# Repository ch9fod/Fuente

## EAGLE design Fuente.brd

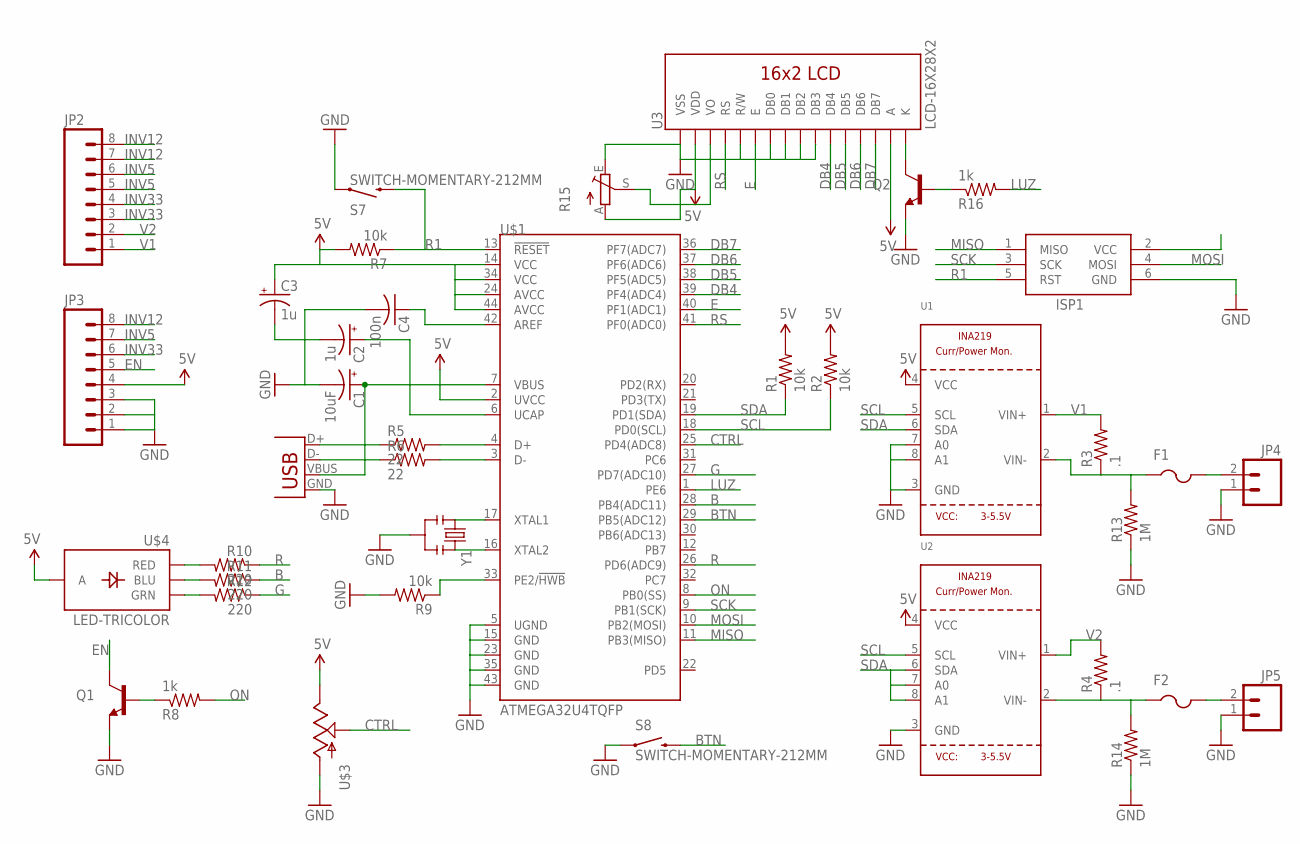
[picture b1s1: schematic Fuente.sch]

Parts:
C1: 10uF; CPOL-RADIAL-10UF-25V
C2, C3: 1u; E2,5-6
C4: 100n; C0805K
F1, F2: PTCFUSE-1812; 1812
ISP1: AVRISP-6; AVRISP
JP1: USBSMD; USB-MINIB
JP2, JP3: M08LONGPADS; 1X08_LONGPADS
JP4, JP5: M02LOCK_LONGPADS; 1X02_LOCK_LONGPADS
Q1, Q2: TRANSISTOR_NPNSOT23; SOT23
R1, R2, R7, R9: 10k; M0805
R3, R4: .1; R2512
R5, R6: 22; 0309/12
R8, R16: 1k; M0805
R10, R11, R12: 220; 0805
R13, R14: 1M; M0805
R15: TRIM_EU-CT6; CT6
S7, S8: SWITCH-MOMENTARY-212MM; TACTILE-PTH-12MM
U1, U2: INA219; SOT23-8
U3: LCD-16X28X2; LCD-8X2
U$1: ATMEGA32U4TQFP; SPARKFUN-DIGITALIC_TQFP44
U$3: POT-RV16AF-20; POT_ALPHA_RV16AF-20
U$4: LED-TRICOLOR; LED-TRICOLOR-SMD
Y1: RESONATORPTH; RESONATOR-PTH

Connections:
5V: C3.+, JP3.4, R1.2, R2.2, R7.2, R15.A, U1.4 (VCC), U2.4 (VCC), U3.2 (VDD), U3.15 (A), U$1.2 (UVCC), U$1.14 (VCC), U$1.24 (AVCC), U$1.34 (VCC), U$1.44 (AVCC), U$3.3 (E), U$4.A
B: R11.1, U$1.28 (PB4(ADC11))
BTN: S8.3 (2), U$1.29 (PB5(ADC12))
CTRL: U$1.25 (PD4(ADC8)), U$3.2 (S)
DB4: U3.11 (DB4), U$1.39 (PF4(ADC4))
DB5: U3.12 (DB5), U$1.38 (PF5(ADC5))
DB6: U3.13 (DB6), U$1.37 (PF6(ADC6))
DB7: U3.14 (DB7), U$1.36 (PF7(ADC7))
E: U3.6 (E), U$1.40 (PF1(ADC1))
EN: JP3.5, Q1.3 (C)
G: R12.1, U$1.27 (PD7(ADC10))
GND: C1.2 (-), C2.-, C3.-, C4.2, ISP1.6 (GND), JP1.GND, JP3.1, JP3.2, JP3.3, JP4.1, JP5.1, Q1.2 (E), Q2.2 (E), R9.2, R13.1, R14.1, R15.E, S7.1, S8.1, U1.3 (GND), U1.7 (A0), U1.8 (A1), U2.3 (GND), U3.1 (VSS), U3.5 (R/W), U3.7 (DB0), U3.8 (DB1), U3.9 (DB2), U3.10 (DB3), U$1.5 (UGND), U$1.15 (GND), U$1.23 (GND), U$1.35 (GND), U$1.43 (GND), U$3.1 (A), Y1.2
INV5: JP2.5, JP2.6, JP3.7
INV12: JP2.7, JP2.8, JP3.8
INV33: JP2.3, JP2.4, JP3.6
LUZ: R16.2, U$1.1 (PE6)
MISO: ISP1.1 (MISO), U$1.11 (PB3(MISO))
MOSI: ISP1.4 (MOSI), U$1.10 (PB2(MOSI))
unnamed: Q1.1 (B), R8.1
unnamed: F2.1, R4.1, R14.2, U2.2 (VIN-)
unnamed: C1.1 (+), JP1.VBUS, U$1.7 (VBUS)
unnamed: R9.1, U$1.33 (PE2/!HWB)
unnamed: R10.2, U$4.R (RED)
unnamed: F1.1, R3.1, R13.2, U1.2 (VIN-)
unnamed: JP1.D+, R5.1
unnamed: R5.2, U$1.4 (D+)
unnamed: R6.2, U$1.3 (D-)
unnamed: JP1.D-, R6.1
unnamed: U$1.17 (XTAL1), Y1.1
unnamed: U$1.16 (XTAL2), Y1.3
unnamed: R11.2, U$4.B (BLU)
unnamed: R12.2, U$4.G (GRN)
unnamed: F1.2, JP4.2
unnamed: F2.2, JP5.2
unnamed: C4.1, U$1.42 (AREF)
unnamed: Q2.1 (B), R16.1
unnamed: R15.S, U3.3 (VO)
unnamed: C2.+, U$1.6 (UCAP)
unnamed: Q2.3 (C), U3.16 (K)
ON: R8.2, U$1.8 (PB0(SS))
R: R10.1, U$1.26 (PD6(ADC9))
R1: ISP1.5 (RST), R7.1, S7.3 (2), U$1.13 (!RESET)
RS: U3.4 (RS), U$1.41 (PF0(ADC0))
SCK: ISP1.3 (SCK), U$1.9 (PB1(SCK))
SCL: R2.1, U1.5 (SCL), U2.5 (SCL), U$1.18 (PD0(SCL))
SDA: R1.1, U1.6 (SDA), U2.6 (SDA), U2.7 (A0), U2.8 (A1), U$1.19 (PD1(SDA))
V1: JP2.1, R3.2, U1.1 (VIN+)
V2: JP2.2, R4.2, U2.1 (VIN+)

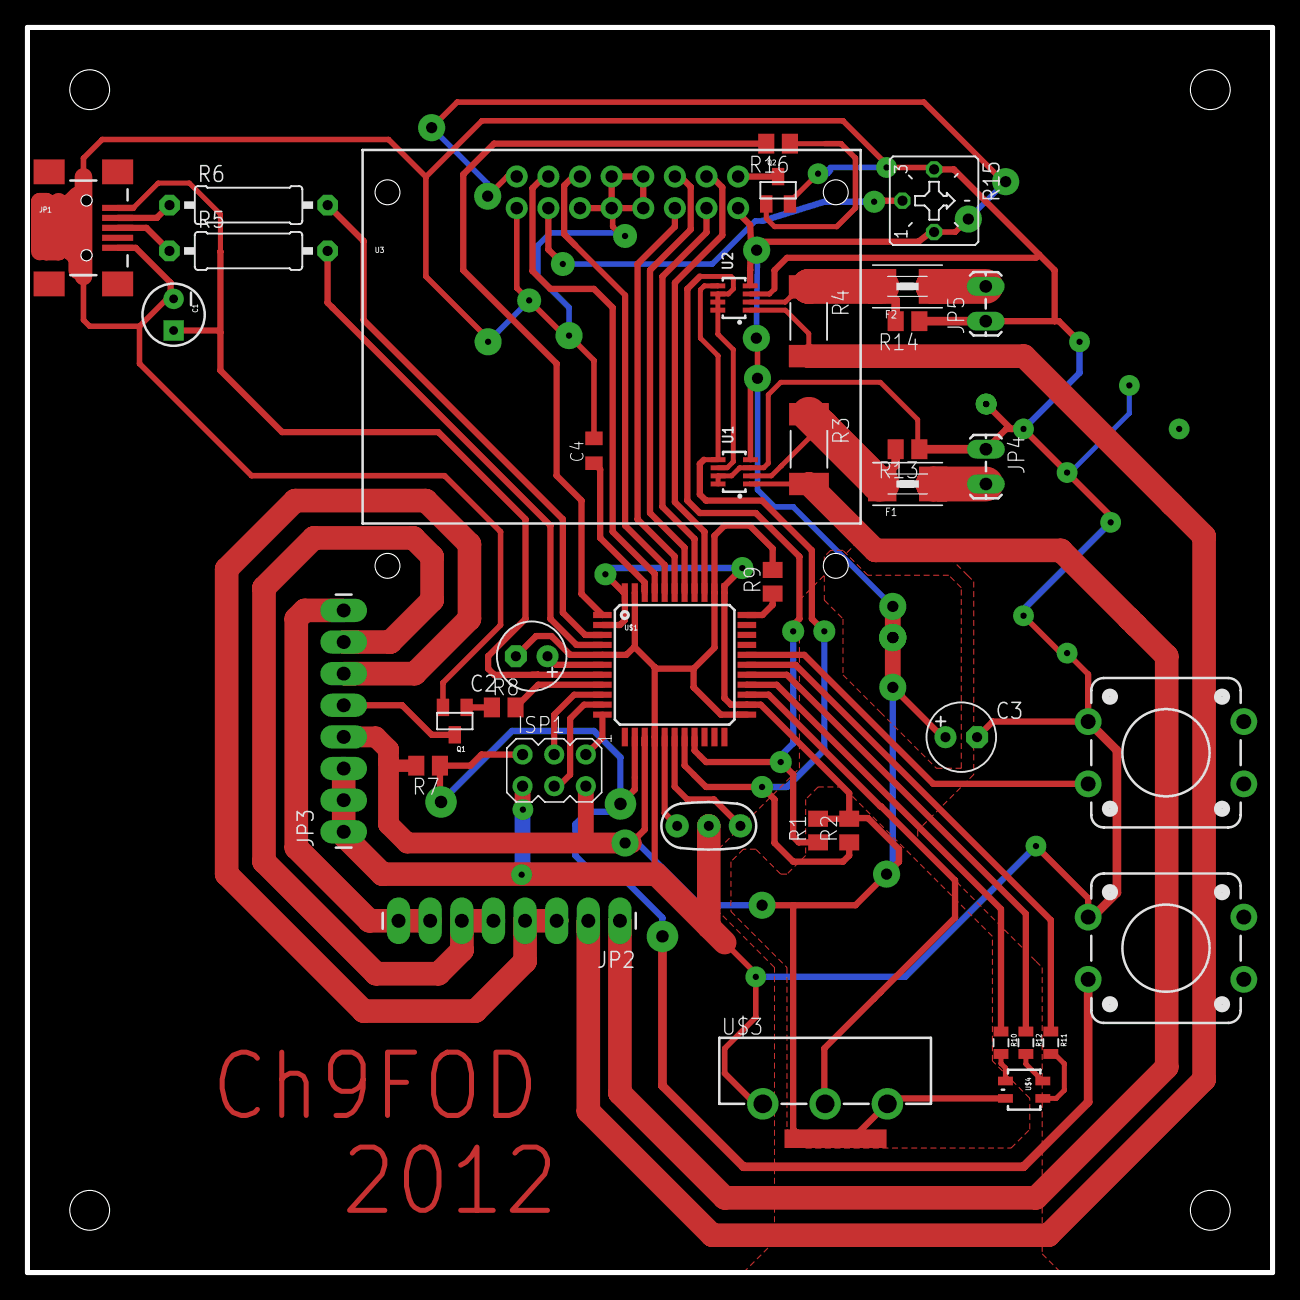
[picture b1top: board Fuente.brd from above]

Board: 2 copper layers, 100.0 x 100.0 mm, 39 parts (0 on the bottom side), 48 nets.

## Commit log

2012-10-06 Power managment for a home made power supply
2012-10-06 Last
2012-11-28 actu
2012-12-03 Sch updated
2012-12-03 Sch and Pcb updated
2012-12-05 pcb and sch updated
2012-12-10 updated pcb and sch
    ready for first print

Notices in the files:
parts and their libraries:
SparkFun-DigitalIC: Licensing: CC v3.0 Share-Alike You are welcome to use this library for commercial purposes.
microbuilder: This work is placed in the public domain, and may be freely used for commercial and non-commercial work with the following conditions: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
